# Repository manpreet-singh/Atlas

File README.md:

# Atlas
Path planner using cubic interpolation

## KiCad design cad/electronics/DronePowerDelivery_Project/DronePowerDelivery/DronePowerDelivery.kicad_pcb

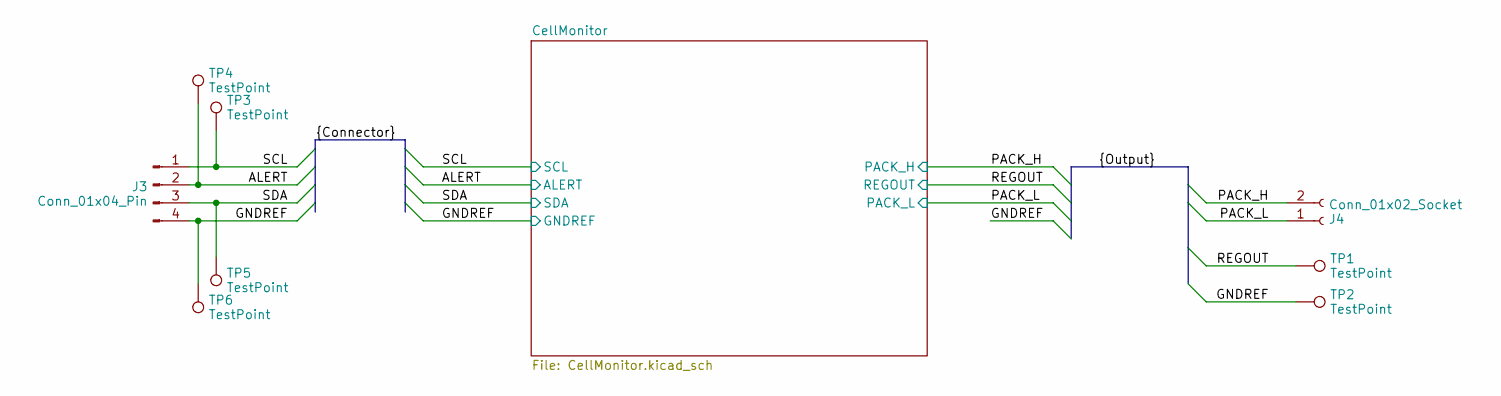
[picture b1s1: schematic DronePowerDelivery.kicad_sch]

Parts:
J3: Conn_01x04_Pin; JST_PH_B4B-PH-K_1x04_P2.00mm_Vertical
J4: Conn_01x02_Socket; AMASS_XT60-M_1x02_P7.20mm_Vertical
TP1, TP2, TP3, TP4, TP5, TP6: TestPoint; TestPoint_Pad_2.0x2.0mm

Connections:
/ALERT: J3.2, TP4.1; also elsewhere on the board
/PACK_H: J4.2; also elsewhere on the board
/PACK_L: J4.1; also elsewhere on the board
/REGOUT: TP1.1; also elsewhere on the board
/SCL: J3.1, TP3.1; also elsewhere on the board
/SDA: J3.3, TP5.1; also elsewhere on the board
GNDREF: J3.4, TP2.1, TP6.1; also elsewhere on the board

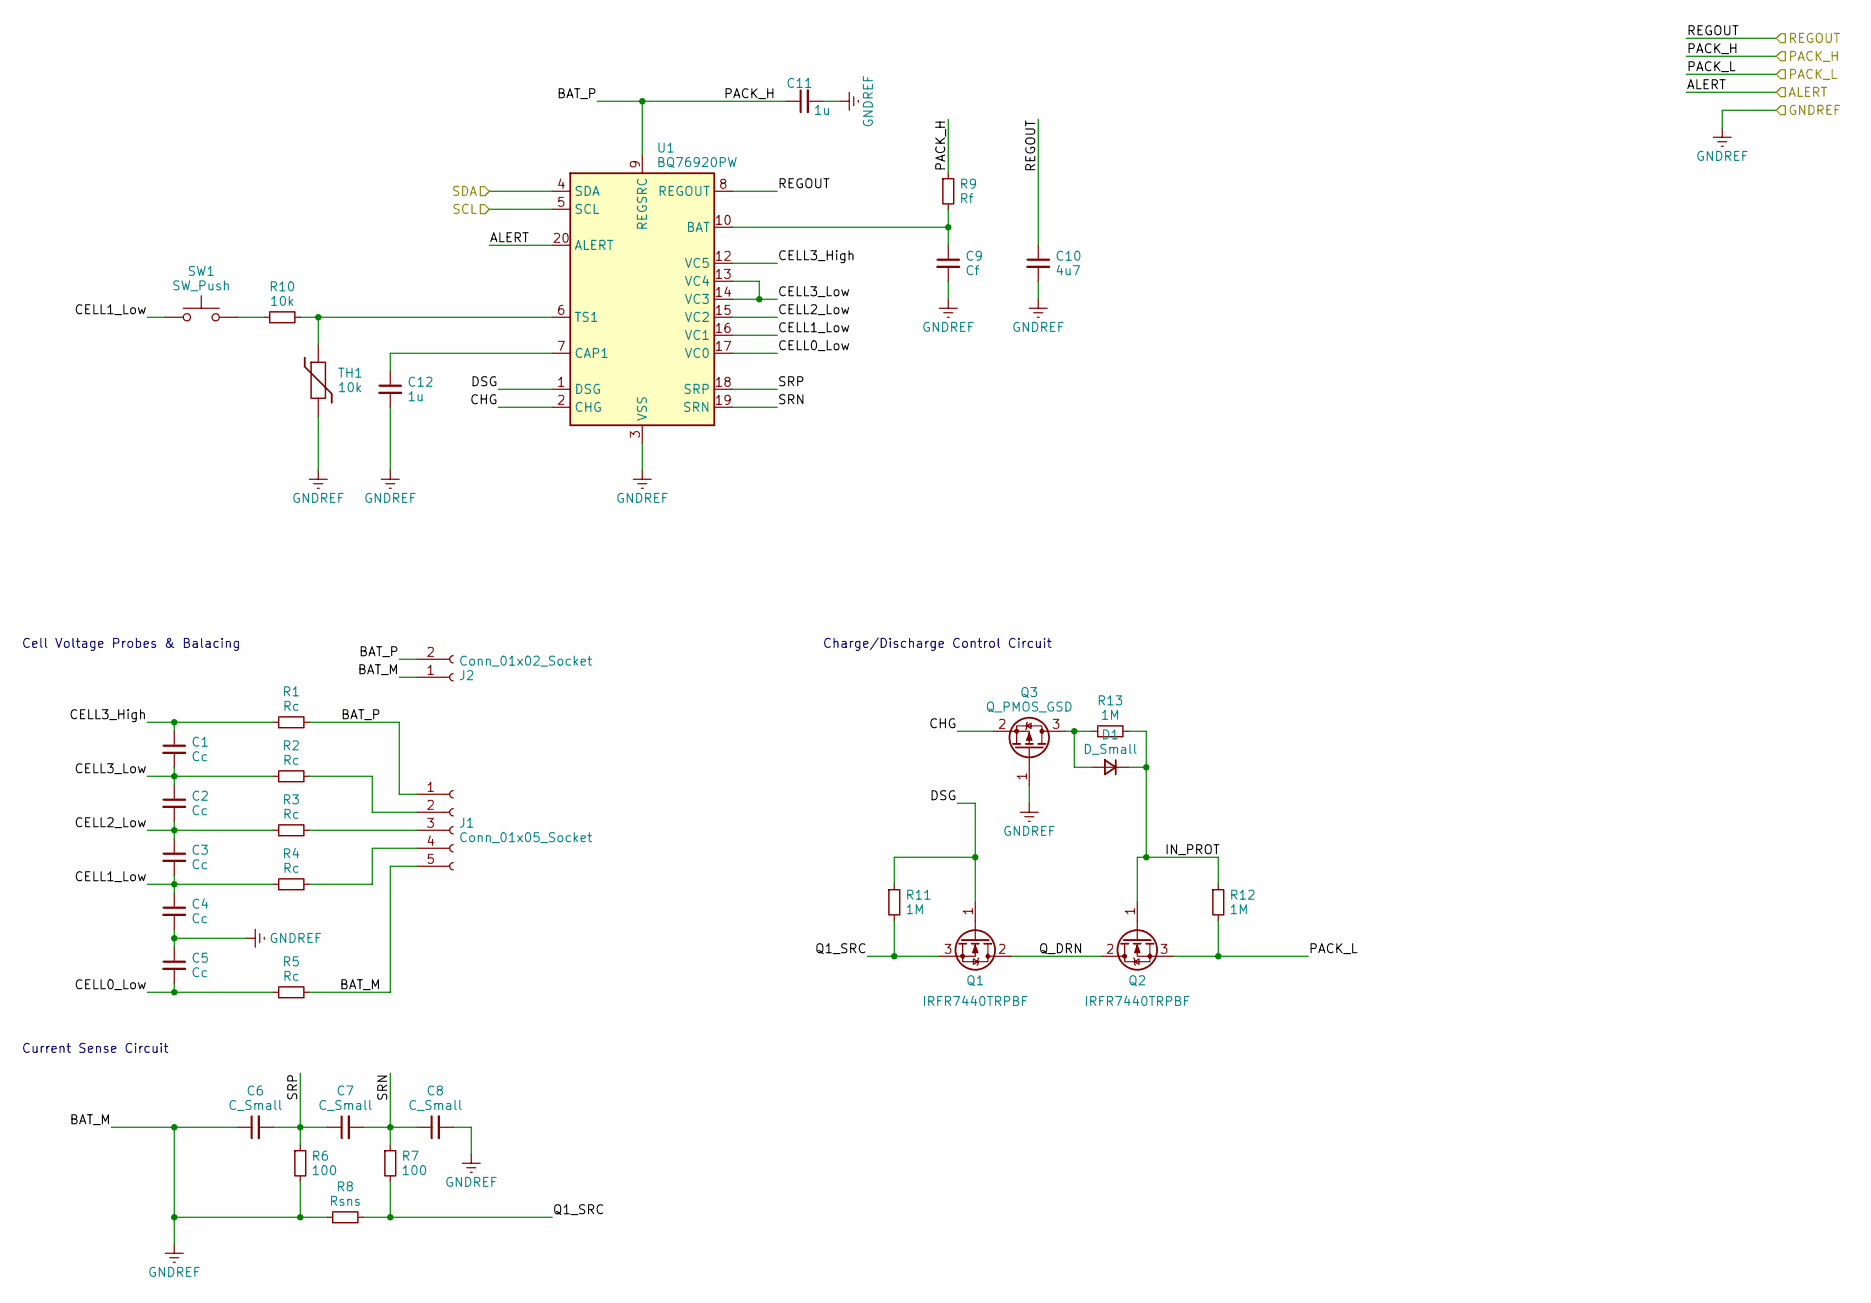
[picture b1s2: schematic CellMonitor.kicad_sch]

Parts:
C1, C2, C3, C4, C5: Cc; C_0603_1608Metric
C6, C7, C8: C_Small; C_0603_1608Metric
C9: Cf; C_0603_1608Metric
C10: 4u7; C_0603_1608Metric
C11, C12: 1u; C_0603_1608Metric
D1: D_Small; D_0603_1608Metric
J1: Conn_01x05_Socket; JST_XH_B5B-XH-A_1x05_P2.50mm_Vertical
J2: Conn_01x02_Socket; AMASS_XT60-F_1x02_P7.20mm_Vertical
Q1, Q2: Q_NMOS_GDS; TO-252-2; Mfg Part# IRFR7440TRPBF; LCSC Part# C97244
Q3: Q_PMOS_GSD; SOT-23; Mfg Part# DMP2305U-7; LCSC Part# C85097
R1, R2, R3, R4, R5: Rc; R_0603_1608Metric
R6, R7: 100; R_0603_1608Metric
R8: Rsns; R_2512_6332Metric
R9: Rf; R_0603_1608Metric
R10: 10k; R_0603_1608Metric
R11, R12, R13: 1M; R_0603_1608Metric
SW1: SW_Push; SW_SPST_EVQP2; Mfg Part# EVQ-P2002W
TH1: 10k; R_0603_1608Metric
U1: BQ76920PW; TSSOP-20_4.4x6.5mm_P0.65mm

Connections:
/ALERT: U1.20 (ALERT); also elsewhere on the board
/CellMonitor/CELL0_Low: C5.2, R5.1, U1.17 (VC0)
/CellMonitor/CELL1_Low: C3.2, C4.1, R4.1, SW1.1, U1.16 (VC1)
/CellMonitor/CELL2_Low: C2.2, C3.1, R3.1, U1.15 (VC2)
/CellMonitor/CELL3_High: C1.1, R1.1, U1.12 (VC5)
/CellMonitor/CELL3_Low: C1.2, C2.1, R2.1, U1.13 (VC4), U1.14 (VC3)
/CellMonitor/CHG: Q3.2 (S), U1.2 (CHG)
/CellMonitor/DSG: Q1.1 (G), R11.1, U1.1 (DSG)
/CellMonitor/IN_PROT: D1.1 (K), Q2.1 (G), R12.1, R13.2
/CellMonitor/Q1_SRC: Q1.3 (S), R7.2, R8.2, R11.2
/CellMonitor/Q_DRN: Q1.2 (D), Q2.2 (D)
/CellMonitor/SRN: C7.2, C8.1, R7.1, U1.19 (SRN)
/CellMonitor/SRP: C6.2, C7.1, R6.1, U1.18 (SRP)
/PACK_H: C11.1, J1.1, J2.2, R1.2, R9.1, U1.9 (REGSRC); also elsewhere on the board
/PACK_L: Q2.3 (S), R12.2; also elsewhere on the board
/REGOUT: C10.1, U1.8 (REGOUT); also elsewhere on the board
/SCL: U1.5 (SCL); also elsewhere on the board
/SDA: U1.4 (SDA); also elsewhere on the board
GNDREF: C4.2, C5.1, C6.1, C8.2, C9.2, C10.2, C11.2, C12.2, J1.5, J2.1, Q3.1 (G), R5.2, R6.2, R8.1, TH1.2, U1.3 (VSS); also elsewhere on the board
unnamed: D1.2 (A), Q3.3 (D), R13.1
unnamed: J1.2, R2.2
unnamed: J1.3, R3.2
unnamed: J1.4, R4.2
unnamed: R10.1, SW1.2
unnamed: C9.1, R9.2, U1.10 (BAT)
unnamed: C12.1, U1.7 (CAP1)
unnamed: R10.2, TH1.1, U1.6 (TS1)

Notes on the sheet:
Charge/Discharge Control Circuit
Cell Voltage Probes & Balacing
Current Sense Circuit

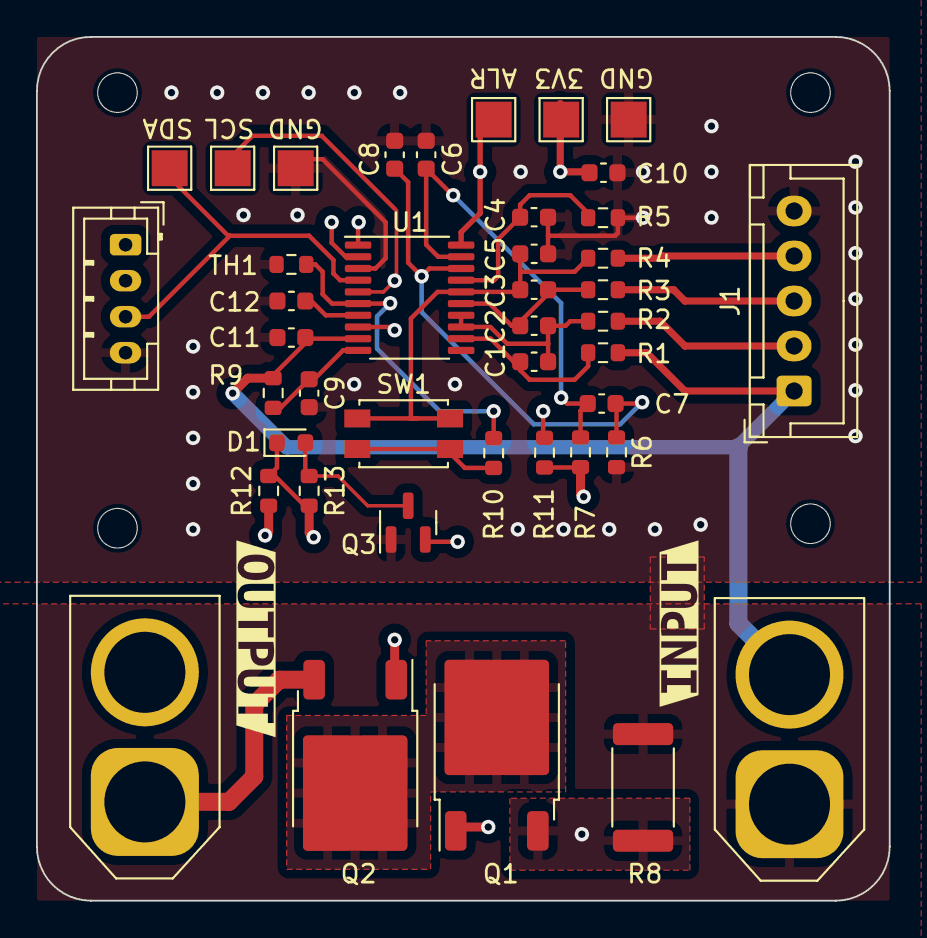
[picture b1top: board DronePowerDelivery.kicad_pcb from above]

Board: 4 copper layers, 47.4 x 48.0 mm, 44 parts (0 on the bottom side), 27 nets.

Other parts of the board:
kibuzzard-64ABA4C5: G***; kibuzzard-64ABA4C5
kibuzzard-64ABA514: G***; kibuzzard-64ABA514

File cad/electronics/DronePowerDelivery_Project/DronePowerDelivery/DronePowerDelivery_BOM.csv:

Id,Designator,Footprint,Quantity,Designation,Mfrg Part,Supplier and ref
1,"C1,C2,C3,C4,C5",C_0603_1608Metric,5,1uf,CL10B105KA8NNNC,https://www.digikey.com/en/products/detail/samsung-electro-m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
2,D1,D_0603_1608Metric,1,D_Small,,
3,"R1,R7,R5,R6,R4,R9,R2,R3",R_0603_1608Metric,8,100,CR0603-FX-1000ELF,https://www.digikey.com/en/products/detail/bourns-inc/CR0603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 
4,"R13,R12,R11",R_0603_1608Metric,3,1M,CRCW06031M00FKEA,https://www.digikey.com/en/products/detail/vishay-dale/CRCW0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 
5,R8,R_2512_6332Metric,1,Rsns,,
6,"R10,TH1",R_0603_1608Metric,2,10k,,
7,SW1,SW_SPST_EVQP2,1,SW_Push,EVQ-P2002W,
8,C10,C_0603_1608Metric,1,4u7,,
9,"C7,C6,C8",C_0603_1608Metric,3,0.1uf,,
10,J2,AMASS_XT60-F_1x02_P7.20mm_Vertical,1,Conn_01x02_Socket,,
11,"Q1,Q2",TO-252-2,2,Q_NMOS_GDS,IRFR7440TRPBF,
12,U1,TSSOP-20_4.4x6.5mm_P0.65mm,1,BQ76920PW,,
13,J4,AMASS_XT60-M_1x02_P7.20mm_Vertical,1,Conn_01x02_Socket,,
14,C9,C_0603_1608Metric,1,10uf,,
15,"C12,C11",C_0603_1608Metric,2,1u,,
16,J1,JST_XH_B5B-XH-A_1x05_P2.50mm_Vertical,1,Conn_01x05_Socket,,
17,J3,JST_PH_B4B-PH-K_1x04_P2.00mm_Vertical,1,Conn_01x04_Pin,,
18,Q3,SOT-23,1,Q_PMOS_GSD,DMP2305U-7,

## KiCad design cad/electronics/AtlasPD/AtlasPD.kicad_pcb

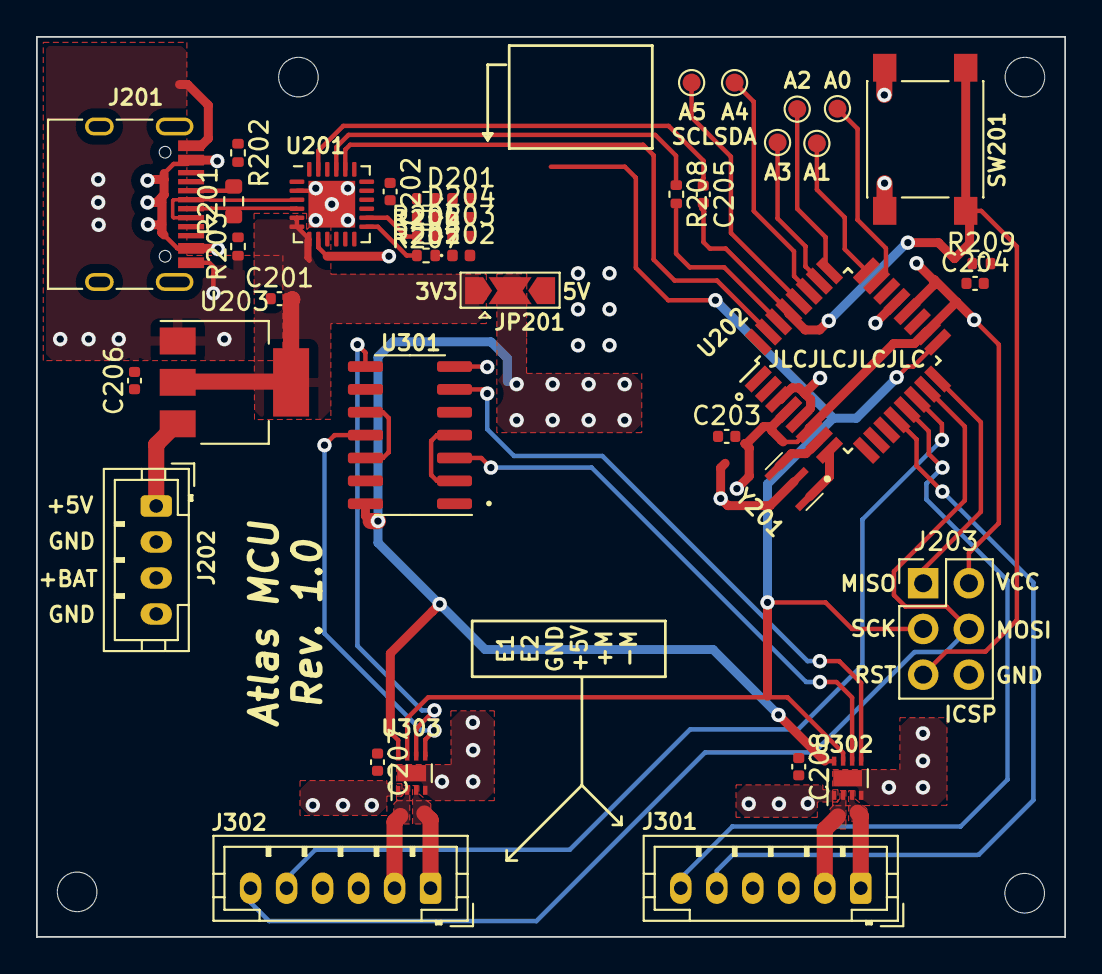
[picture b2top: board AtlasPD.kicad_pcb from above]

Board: 4 copper layers, 57.1 x 50.0 mm, 41 parts (0 on the bottom side), 46 nets.

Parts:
C201, C203, C204, C205: 0.1uF; C_0402_1005Metric
C202, C206: 10uF; C_0402_1005Metric
C207, C208: 10u; C_0402_1005Metric
D201: YELLOW; LED_0402_1005Metric
D202, D203: RED; LED_0402_1005Metric
D204: GREEN; LED_0402_1005Metric
J201: USB_C_Receptacle_USB2.0; USB_C_Receptacle_HRO_TYPE-C-31-M-12
J202: Conn_01x04; JST_PH_B4B-PH-K_1x04_P2.00mm_Vertical
J203: Conn_02x03_Odd_Even; PinHeader_2x03_P2.54mm_Vertical
J301, J302: Conn_01x06; JST_PH_B6B-PH-K_1x06_P2.00mm_Vertical
JP201: SolderJumper_3_Open; SolderJumper-3_P2.0mm_Open_TrianglePad1.0x1.5mm
R201: 0; R_0603_1608Metric
R202, R203: 5.11K; R_0402_1005Metric
R204, R207: 1k; R_0402_1005Metric
R205, R206, R208: 1K; R_0402_1005Metric
R209: 10K; R_0402_1005Metric
SW201: SW_SPST; SW_Push_1P1T_NO_6x6mm_H9.5mm
TP201, TP202, TP203, TP204, TP205, TP206: TestPoint_Alt; TestPoint_Pad_D1.0mm
U201: CP2104; QFN-24-1EP_4x4mm_P0.5mm_EP2.6x2.6mm
U202: ATmega328P-AU; TQFP-32_7x7mm_P0.8mm
U203: AMS1117-3.3; SOT-223-3_TabPin2
U301: 74LS08; SOIC-14_3.9x8.7mm_P1.27mm
U302, U303: DRV8837C; WSON-8-1EP_2x2mm_P0.5mm_EP0.9x1.6mm
Y201: 16MHz; CSTNE16M0V530000R0

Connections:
+3V3: C201.2, C206.1, JP201.1 (A), U201.5 (VIO), U201.6 (VDD), U201.7 (REGIN), U203.2 (VO)
+5V: D202.2 (A), D203.2 (A), D204.2 (A), J201.A4 (VBUS), J201.A9 (VBUS), J201.B4 (VBUS), J201.B9 (VBUS), J202.1, J301.3, J302.3, JP201.3 (B), U201.8 (VBUS), U203.3 (VI)
+BATT: J202.3, U302.1 (VM)
/Motor Driver/+M1: J301.2, U302.2 (OUT1)
/Motor Driver/+M2: J302.2, U303.2 (OUT1)
/Motor Driver/-M1: J301.1, U302.3 (OUT2)
/Motor Driver/-M2: J302.1, U303.3 (OUT2)
/Motor Driver/~SLEEP: D201.2 (A), J203.3, U202.17 (PB5), U302.7 (~SLEEP), U303.7 (~SLEEP)
/Sheet60A2E58A/AD0: TP206.1, U202.23 (PC0)
/Sheet60A2E58A/AD1: TP205.1, U202.24 (PC1)
/Sheet60A2E58A/AD2: TP204.1, U202.25 (PC2)
/Sheet60A2E58A/AD3: TP203.1, U202.26 (PC3)
/Sheet60A2E58A/AD4_SDA: TP202.1, U202.27 (PC4)
/Sheet60A2E58A/AD5_SCL: TP201.1, U202.28 (PC5)
/Sheet60A2E58A/DTR: C205.1, U201.23 (~DTR)
/Sheet60A2E58A/IO0: R208.2, U202.30 (PD0)
/Sheet60A2E58A/IO1: U201.20 (RXD), U202.31 (PD1)
/Sheet60A2E58A/IO2: U202.32 (PD2), U301.5, U302.6 (IN1)
/Sheet60A2E58A/IO3: U202.1 (PD3), U301.1, U302.5 (IN2)
/Sheet60A2E58A/IO4: U202.2 (PD4), U301.2, U301.4
/Sheet60A2E58A/IO5: U202.9 (PD5), U301.9, U303.6 (IN1)
/Sheet60A2E58A/IO6: U202.10 (PD6), U301.13, U303.5 (IN2)
/Sheet60A2E58A/IO7: U202.11 (PD7), U301.10, U301.12
/Sheet60A2E58A/IO8: J301.5, U202.12 (PB0)
/Sheet60A2E58A/IO9: J301.6, U202.13 (PB1)
/Sheet60A2E58A/IO10_SS: J302.5, U202.14 (PB2)
/Sheet60A2E58A/IO11_MOSI: J203.4, J302.6, U202.15 (PB3)
/Sheet60A2E58A/IO12_MISO: J203.1, U202.16 (PB4)
/Sheet60A2E58A/RESET: C205.2, J203.5, R209.1, SW201.1 (A), U202.29 (~RESET/PC6)
/Sheet60A2E58A/RXD: R208.1, U201.21 (TXD)
/Sheet60A2E58A/USB_DN: J201.A7 (D-), R201.1, U201.4 (D-)
/Sheet60A2E58A/USB_DP: J201.A6 (D+), J201.B6 (D+), U201.3 (D+)
GND: C201.1, C202.1, C203.1, C204.1, C206.2, C207.2, C208.2, J201.A1 (GND), J201.A12 (GND), J201.B1 (GND), J201.B12 (GND), J202.2, J202.4, J203.6, J301.4, J302.4, R202.1, R203.1, R204.2, R207.2, SW201.2 (B), U201.2 (GND), U201.25 (GND), U202.3 (GND), U202.5 (GND), U202.21 (GND), U203.1 (GND), U301.7 (GND), U302.4 (GND), U302.9 (GND), U303.4 (GND), U303.9 (GND), Y201.2
unnamed: C202.2, U201.16 (VPP)
unnamed: D201.1 (K), R204.1
unnamed: D202.1 (K), R205.2
unnamed: D203.1 (K), R206.2
unnamed: D204.1 (K), R207.1
unnamed: J201.A5 (CC1), R202.2
unnamed: J201.B5 (CC2), R203.2
unnamed: J201.B7 (D-), R201.2
unnamed: R205.1, U201.13 (RXT/GPIO.1)
unnamed: R206.1, U201.14 (TXT/GPIO.0)
unnamed: U202.7 (XTAL1/PB6), Y201.3
unnamed: U202.8 (XTAL2/PB7), Y201.1
VCC: C203.2, C204.2, C207.1, C208.1, J203.2, JP201.2 (C), R209.2, U202.4 (VCC), U202.6 (VCC), U202.18 (AVCC), U202.20 (AREF), U301.14 (VCC), U302.8 (VCC)

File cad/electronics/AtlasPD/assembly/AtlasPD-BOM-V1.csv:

Comment,Designator,Footprint,LCSC
0.1uF,"C201,C203,C204,C205",Capacitor_SMD:C_0603_1608Metric,C14663
10uF,"C202,C403",Capacitor_SMD:C_0603_1608Metric,C96446
YELLOW,D201,LED_SMD:LED_0603_1608Metric,C72038
RED,"D202,D203",LED_SMD:LED_0603_1608Metric,C2286
GREEN,D204,LED_SMD:LED_0603_1608Metric,C72043
USB_C_Receptacle_USB2.0,J201,Connector_USB:USB_C_Receptacle_HRO_TYPE-C-31-M-12,C165948
5.11K,"R202,R203",Resistor_SMD:R_0603_1608Metric,C112314
1k,"R204,R207",Resistor_SMD:R_0603_1608Metric,C21190
1K,"R205,R206,R208",Resistor_SMD:R_0603_1608Metric,C21190
10K,R209,Resistor_SMD:R_0603_1608Metric,C25804
SW_SPST,SW201,Button_Switch_SMD:SW_Push_1P1T_NO_6x6mm_H9.5mm,C318884
CP2104,U201,Package_DFN_QFN:QFN-24-1EP_4x4mm_P0.5mm_EP2.6x2.6mm,C47742
ATmega328P-AU,U202,Package_QFP:TQFP-32_7x7mm_P0.8mm,C14877
74LS08,U301,Package_SO:SOIC-14_3.9x8.7mm_P1.27mm,C5593
DRV8837C,"U302,U303",Package_SON:WSON-8-1EP_2x2mm_P0.5mm_EP0.9x1.6mm,C191000
CSTNE16M0V53-R0,Y201,SamacSys_Parts:CSTNE16M0V530000R0,C341521

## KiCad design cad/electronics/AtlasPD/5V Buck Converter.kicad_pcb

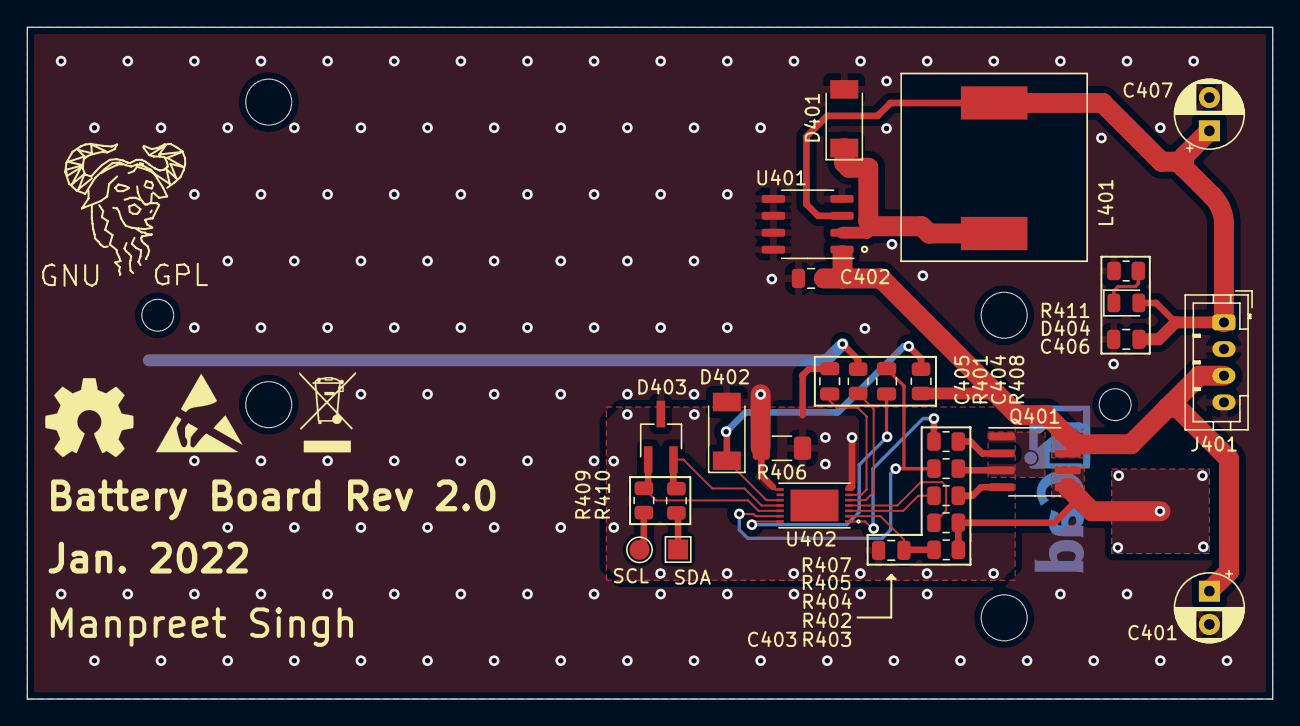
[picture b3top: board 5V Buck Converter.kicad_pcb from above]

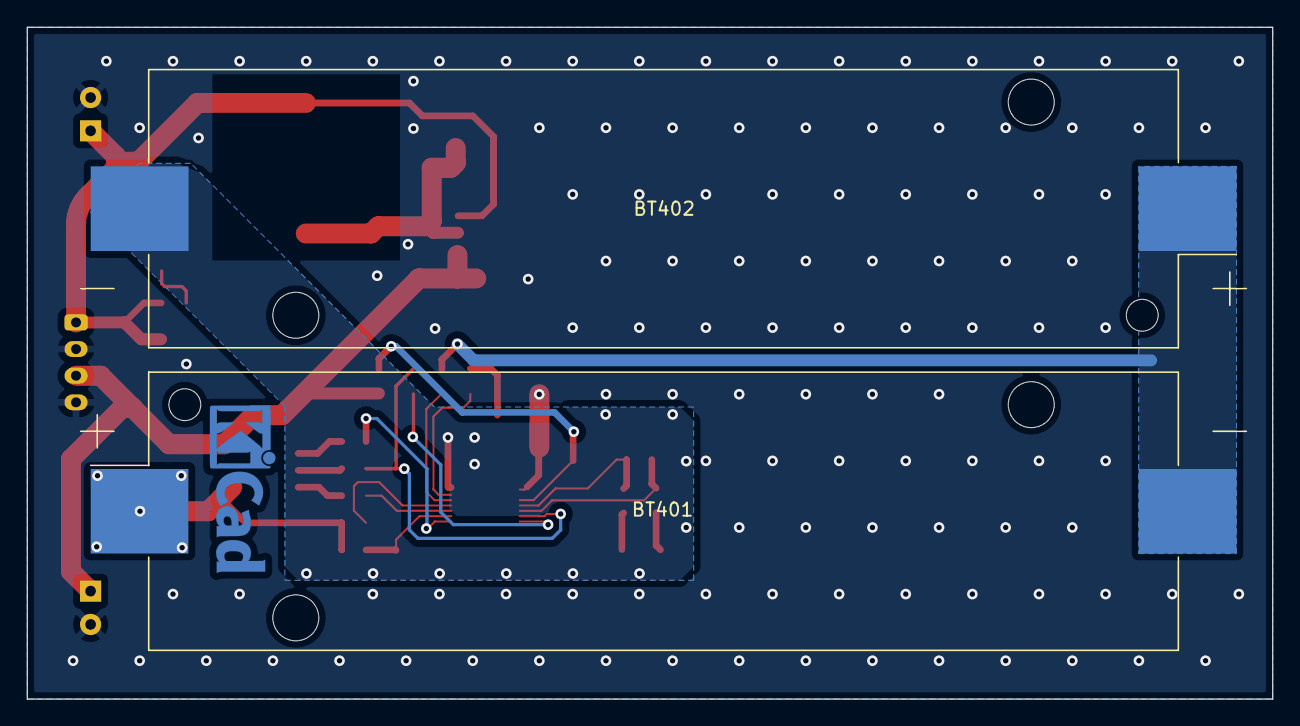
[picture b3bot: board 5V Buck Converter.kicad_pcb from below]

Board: 2 copper layers, 93.5 x 50.4 mm, 31 parts (2 on the bottom side), 24 nets.

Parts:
BT401, BT402: Battery_Cell; BatteryHolder_Keystone_1042_1x18650
C401, C407: 220uF; CP_Radial_D5.0mm_P2.50mm
C402, C406: 10uF; C_0805_2012Metric
C403, C405: 0.1u; C_0805_2012Metric
C404: 0.47u; C_0805_2012Metric
D401, D402: D_Schottky; D_SOD-128
D403: D_Zener_Dual_CommonAnode_KKA_Parallel; TSOT-23_HandSoldering
D404: LED; LED_0805_2012Metric
J401: Conn_01x04; JST_PH_B4B-PH-K_1x04_P2.00mm_Vertical
L401: 39 uH; CDRH127
Q401: Q_Dual_NMOS_S1G1S2G2D2D2D1D1; SOIC-8_3.9x4.9mm_P1.27mm
R401, R402, R404, R407, R408, R411: 1k; R_0805_2012Metric
R403, R409, R410: 150; R_0805_2012Metric
R405: 470; R_0805_2012Metric
R406: 20m; R_1206_3216Metric_Pad1.30x1.75mm_HandSolder
TP401: SDA; TestPoint_Pad_1.5x1.5mm
TP402: SCL; TestPoint_Pad_D1.5mm
U401: AP1509-50SG-13; SO-8_3.9x4.9mm_P1.27mm
U402: DS2777; DS2777G+

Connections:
+5V: C406.1, C407.1, D404.2 (A), J401.1, L401.2, U401.3 (FB)
+BATT: C401.1, C402.1, J401.3, Q401.7 (D), Q401.8 (D), R408.1, U401.1 (Vin)
/BT_VDD: BT401.1 (+), Q401.5 (D), Q401.6 (D), R402.1, R403.1
/Q_SRC: Q401.1 (S), Q401.3 (S), R405.1
/SCL: R409.2, TP402.1
/SDA: R410.2, TP401.1
/SRC: C404.2, R405.2, U402.13 (SRC)
GND: C401.2, C402.2, C406.2, C407.2, D401.2 (A), D402.2 (A), D403.3 (A), J401.2, J401.4, R406.2, R411.2, U401.4 (SD), U401.5 (GND), U401.6 (GND), U401.7 (GND), U401.8 (GND), U402.8 (SNS)
GNDPWR: BT402.2 (-), C403.2, C405.2, R406.1, U402.7 (VSS)
unnamed: BT401.2 (-), BT402.1 (+), R401.1
unnamed: C403.1, R403.2, U402.2 (VDD)
unnamed: C404.1, U402.14 (CP)
unnamed: C405.1, U402.6 (VB)
unnamed: D401.1 (K), L401.1, U401.2 (SW)
unnamed: D402.1 (K), R408.2, U402.10 (PLS)
unnamed: D403.1 (K), R409.1, U402.12 (SCL)
unnamed: D403.2 (K), R410.1, U402.11 (SDA)
unnamed: D404.1 (K), R411.1
unnamed: Q401.2 (G), R407.1
unnamed: Q401.4 (G), R404.1
unnamed: R401.2, U402.5 (VIN1)
unnamed: R402.2, U402.4 (VIN2)
unnamed: R404.2, U402.3 (DC)
unnamed: R407.2, U402.1 (CC)

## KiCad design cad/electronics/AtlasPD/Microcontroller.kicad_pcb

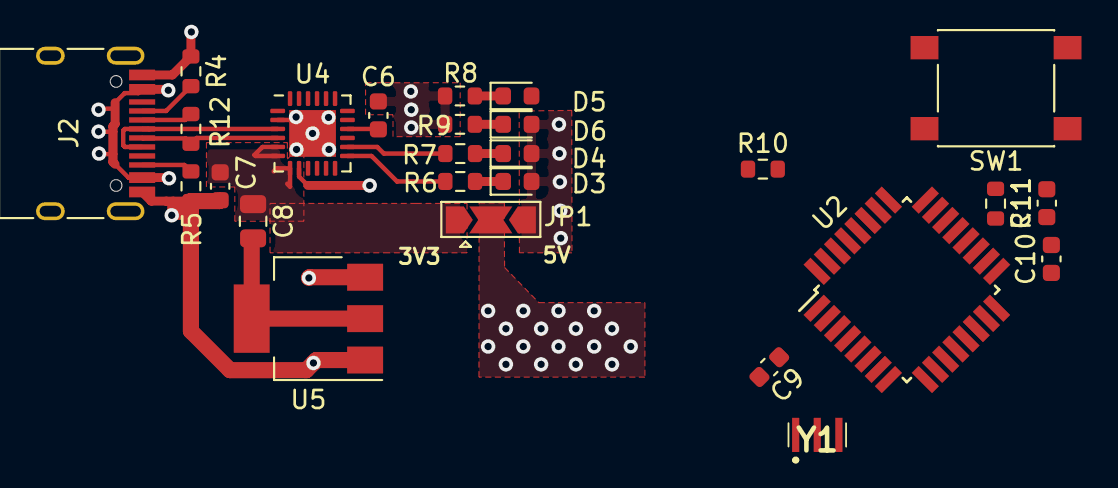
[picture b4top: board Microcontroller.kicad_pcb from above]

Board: 2 copper layers, 26 parts (0 on the bottom side), 26 nets.

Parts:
C6: 10uF; C_0603_1608Metric
C7, C9, C10, C11: 0.1uF; C_0603_1608Metric
C8: 10uF; C_0805_2012Metric
D3, D4: RED; LED_0603_1608Metric
D5: YELLOW; LED_0603_1608Metric
D6: GREEN; LED_0603_1608Metric
J2: USB_C_Receptacle_USB2.0; USB_C_Receptacle_HRO_TYPE-C-31-M-12
JP1: SolderJumper_3_Open; SolderJumper-3_P2.0mm_Open_TrianglePad1.0x1.5mm
R4, R5: 5.11K; R_0603_1608Metric
R6, R7, R10: 1K; R_0603_1608Metric
R8, R9: R; R_0603_1608Metric
R11: 10K; R_0603_1608Metric
R12: 0; R_0603_1608Metric
SW1: SW_SPST; SW_Push_1P1T_NO_6x6mm_H9.5mm
U2: ATmega328P-AU; TQFP-32_7x7mm_P0.8mm
U4: CP2104; QFN-24-1EP_4x4mm_P0.5mm_EP2.6x2.6mm
U5: AMS1117-3.3; SOT-223-3_TabPin2
Y1: CSTNE16M0V53-R0; CSTNE16M0V530000R0

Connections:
+3V3: C7.2, JP1.1, U4.5, U4.6, U4.7
+5V: D3.2, D4.2, D6.2, J2.A4, J2.A9, J2.B4, J2.B9, JP1.3, U4.8
/DTR: C11.1, U4.23
/IO0: R10.2, U2.30
/IO1: U2.31, U4.21
/IO13_SCK: D5.2, U2.17
/RXD: R10.1, U4.20
/USB_DN: J2.A7, R12.1, U4.4
/USB_DP: J2.A6, J2.B6, U4.3
GND: C6.1, C7.1, J2.A1, J2.A12, J2.B1, J2.B12, R4.1, R5.1, R8.2, R9.2, SW1.2, U2.3, U2.5, U2.21, U4.2, U4.25, Y1.2
unnamed: C6.2, U4.16
unnamed: C9.1, U2.4, U2.6
unnamed: C10.1, U2.18
unnamed: C11.2, R11.1, SW1.1, U2.29
unnamed: D3.1, R6.2
unnamed: D4.1, R7.2
unnamed: D5.1, R8.1
unnamed: D6.1, R9.1
unnamed: J2.A5, R4.2
unnamed: J2.B5, R5.2
unnamed: J2.B7, R12.2
unnamed: R6.1, U4.13
unnamed: R7.1, U4.14
unnamed: U2.7, Y1.3
unnamed: U2.8, Y1.1
VCC: C9.2, C10.2, JP1.2, R11.2, U2.20

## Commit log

2018-07-10 Adding files to project
2018-07-11 Removed test code
2018-07-11 Split classes into declaration and implementation. Fixed variable escaping scope bug.
2018-07-14 Added Path Class
2018-07-27 Worked on adding calcuations for the length function
2018-07-27 Fixed calculation error
2018-07-27 Implemented the calculations class
2018-08-02 Some Cleanup and some more implementations
2018-08-02 Create LICENSE
2018-08-03 No longer getting segfaults :+1:
2018-08-03 Fixed spline coefficient generating function
2018-08-15 Added Process Diagram.xml
2018-08-15 Rename Untitled Diagram.xml to Process Diagram.xml
2018-09-12 Testing out the path generation algorithm via SFML graphics
2019-07-11 Project Restructuring
2019-07-11 Started Restrusturing the Code itself
2019-07-11 Moved unessesary class
2019-07-12 Further Restructuring and started adding fiemware code to control the hardware
2019-07-18 Some more work on the beaglebone code
2019-07-19 Added GPIO Implementation Code
2019-07-19 Added read function for GPIO input
2019-09-13 Started work on H-Bridge driver
2019-10-14 Removed Macro and Tested GPIO functionality
2020-03-27 Started adding PWM firmware
2020-03-29 Added PWM implemention
2020-05-03 Swtiched over to using the adafruit libraries for GPIO and PWM
2020-05-03 Additional changes to the L298N Driver, Deprecated the old PWM and GPIO drivers
2020-05-24 Testing the motor driver on the Beaglebone
2020-05-24 Added Exception handling
2020-05-24 Added missing PWM initialization
2020-05-24 Adjusted some parameters
2020-05-24 Adjusted CMakeList since crosscompiling won't work with dependencies
2020-05-26 Testing frequency change for PWM
2020-05-26 Last attempt to change PWM freuqency failed, trying different approach
2020-05-26 Finally fiqured out how to initialize the PWM channels with a variable frequency
2020-06-17 Added debug info for pin states
2020-06-17 Nevermind
2020-06-17 Added internal debug logging from the bbio libraries
2020-10-01 Started adding code to communicate with Arduino over I2C
2020-12-19 i2c test code
2021-02-01 Added placeholder PCB files
2021-03-24 Added Buck Converter
2021-03-29 Finished Basic Buck Converter Design
2021-08-17 Pushing latest changes
2021-08-19 Untracked changes
2021-08-26 Started adding ROS stuff to Arduino, Started Laying out Electrical Diagram
2021-09-11 Latest changes
2021-09-11 Added motor test
2021-09-15 Added LDO
2021-09-15 Added part annotations
2021-09-16 PCB Changes to 5V Regulator
2021-09-16 Removed file
2021-09-16 More PCB changes
2021-09-17 Prep for short run production of power converter
2021-10-07 More Electronics design work
2021-10-08 Started layout
2021-10-08 Forgot to save changes
2021-10-08 Layout updates, new PMICs for motors
2021-10-08 Added logic gates
2021-10-08 Project Restructuring for ease of design and other stuff
2021-10-12 Found a bug, squashed it
2021-10-13 Power board layout
2021-10-15 First Board Layout done
2021-10-15 Additional layout chaneges, and added testpoints
2021-10-20 Layout updates
2021-10-21 Moved MCU a bit closer to the USB
2021-10-21 Small Changes
2021-10-25 Small Layout Changes
2021-10-25 Getting Ready to Fab MCU
2021-10-25 Adding a updated design schematic
2021-10-28 Preliminary PCB Production files
2021-11-05 Adding docs page
2021-11-05 Set theme jekyll-theme-cayman
2021-11-05 Started Adding docs and stuff man
2021-11-05 Added option to choose between my own lib and adafruit lib
2021-11-05 Update licence
2021-11-16 JLC Restock, they now have 16Mhz crystals, need to adjust fabrication outputs
2021-11-19 Mini update
2021-11-22 Some code updates to motor test file
2021-11-23 Motor test feature updates, queued for testing on hardware
2021-11-30 Chaning MCU board size for better layout
2021-11-30 Forgot to save schematic
2021-11-30 Arduino file changes
2021-12-02 New PCB Layout
2021-12-03 Battery board changes
2021-12-03 More changes to battery board, preping for manufacturing
2021-12-05 Battery board sent to fab
2021-12-08 5V Regulator changes
2021-12-08 Battery board Rev 1.5
2021-12-09 CMake build now operational again
2022-01-03 KiCad 6.0 upgrade
2022-01-07 Started adding battery protection and fuel guage design
2022-01-12 Finished IC Schematic, Assigned footprints
2022-01-12 Forgot to save
2022-01-12 Fixed schematic issues from KiCAD upgrade, Moved 3.3V LDO to MCU Sheet
2022-01-13 Small changes, saving what I have
2022-01-13 Finished Battery Board V2 PCB Layout
2022-01-14 Small Tweaks
2022-01-14 Refined PCB design, want to do final review later on before sending to Fab
2022-01-14 Simplified design layout
2022-01-15 Battery Enclosure
2022-02-05 Shifting to PIO projects for Arduino development
2022-03-04 Added DS2778 Memory Map
2022-04-19 Small Update
2022-04-19 update docs
2022-04-19 Added some photos
2022-04-19 Fixed Small Error
2022-04-19 one line change
2022-04-25 3d stencil files
2022-04-25 Ignoring Unessesary Files
2022-04-25 Removed more useless files
2022-04-28 Changing MCU design due to chip shortage affecting current design/plans
2022-04-29 Eliminated need for AND gate IC
2022-05-03 Layout updates for MKR
2022-05-27 Small update to README.md
2022-06-08 Added Altium project for STM MCU
2022-06-08 3.3V Regulator layed out
2022-06-24 Finalized HSE Design
2022-07-06 Added SWD
2022-07-06 added additional .gitignore
2022-07-07 Added MPU6050
2022-07-11 More Circuit Protection, more passives
2022-07-12 Started Component placement
2022-07-13 Redefined some connections to better fit component placement
2022-07-14 Started PCB Layout
2022-07-15 Fixed some typos, added some PDFs
2022-07-21 more layout added, Discovered issue with I2C Connector, need to rewire
2022-07-22 First revision of PCB laid out
2022-07-25 Finalized Rev 0.1 Layout, Going to attempt order
2022-07-27 Some more progress on PCB layout, More work on C/C++ Driver
2022-07-29 Rev 0.1 of AtlasSTM32_MCU GO
2022-08-10 Added Photos, Started Fixing Bugs for a potential revision to stm-cerberus
2022-08-10 More Rev 0.2 changes
2022-08-12 Documentation updates
2022-08-12 Finally managed to fix image
2022-08-12 Added Revision 0.2 Changelog
2022-08-17 Added breakout pads to most of Port B on the STM32
2022-09-14 more photos and docs
2023-06-30 Starting to add new power delivery project files
2023-07-02 Added additional schematic capture
2023-07-05 Finialized Component Sizing
2023-07-08 Rev.1 of PCB laid out
2023-07-10 Finalied Rev1 Layout
2023-07-13 Finished and ordered Rev1 of DronePD PCB
2023-07-21 Assigned component values
2023-07-29 Added BOM
2023-08-01 Finalized BOM
2024-01-28 Initialization Scripts
2024-01-28 Basic Initialization script to enable discharging
2024-07-03 Uploading changes

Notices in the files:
parts and their libraries:
Copyright 2021 Accelerated Designs. All rights reserved.
